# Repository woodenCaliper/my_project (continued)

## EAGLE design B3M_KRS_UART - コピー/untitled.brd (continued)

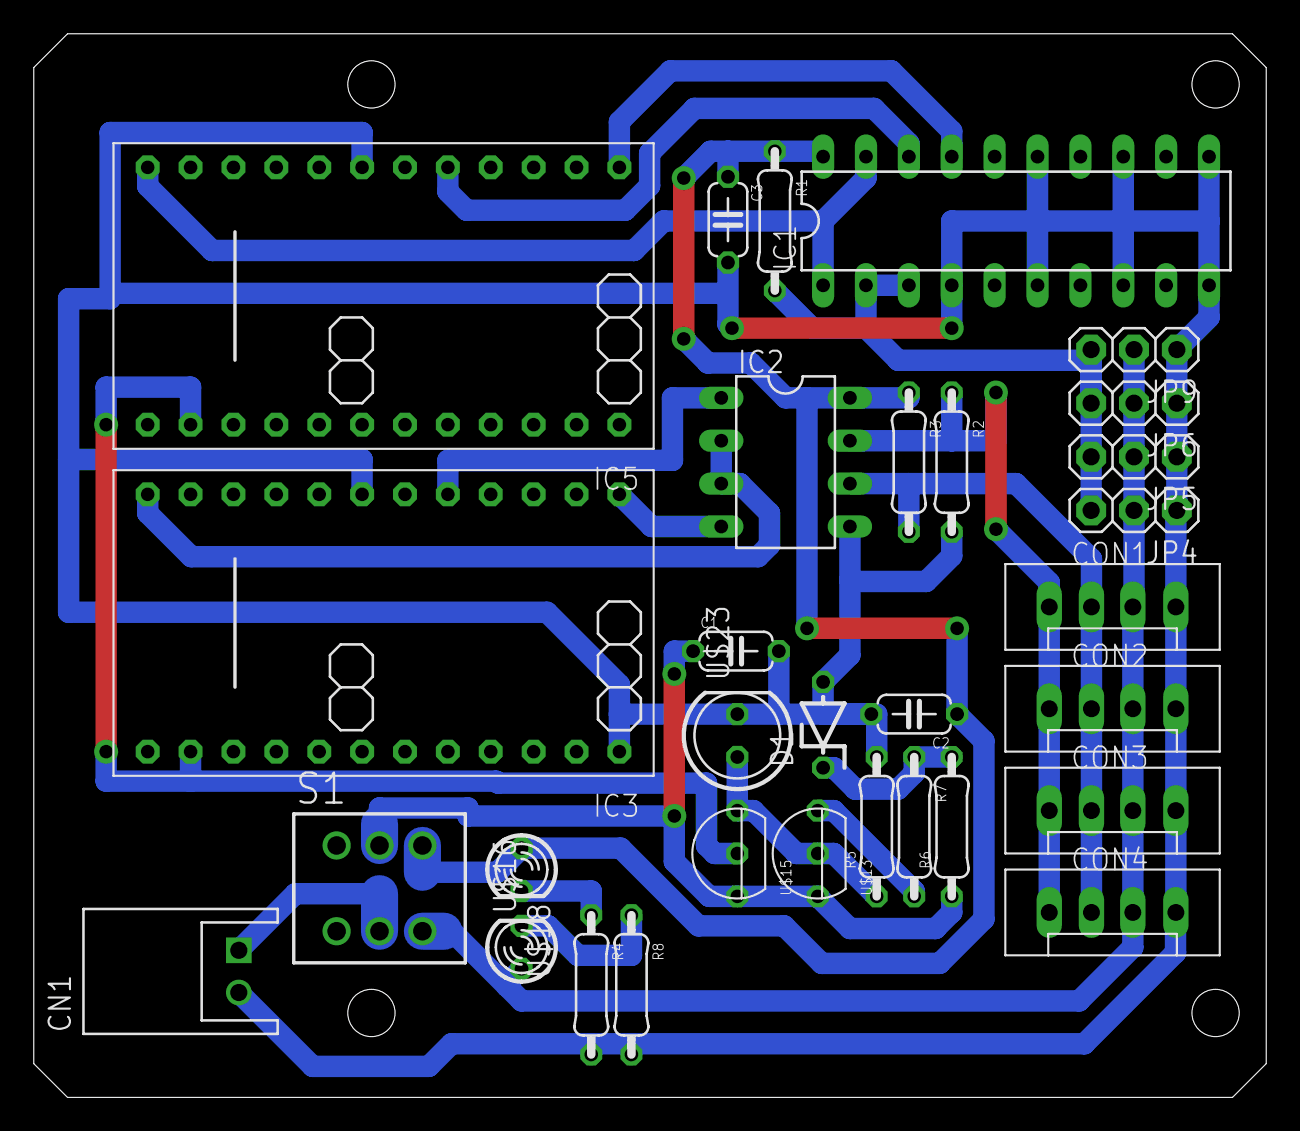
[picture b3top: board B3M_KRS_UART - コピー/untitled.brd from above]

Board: 2 copper layers, 73.0 x 63.0 mm, 31 parts (0 on the bottom side), 20 nets.

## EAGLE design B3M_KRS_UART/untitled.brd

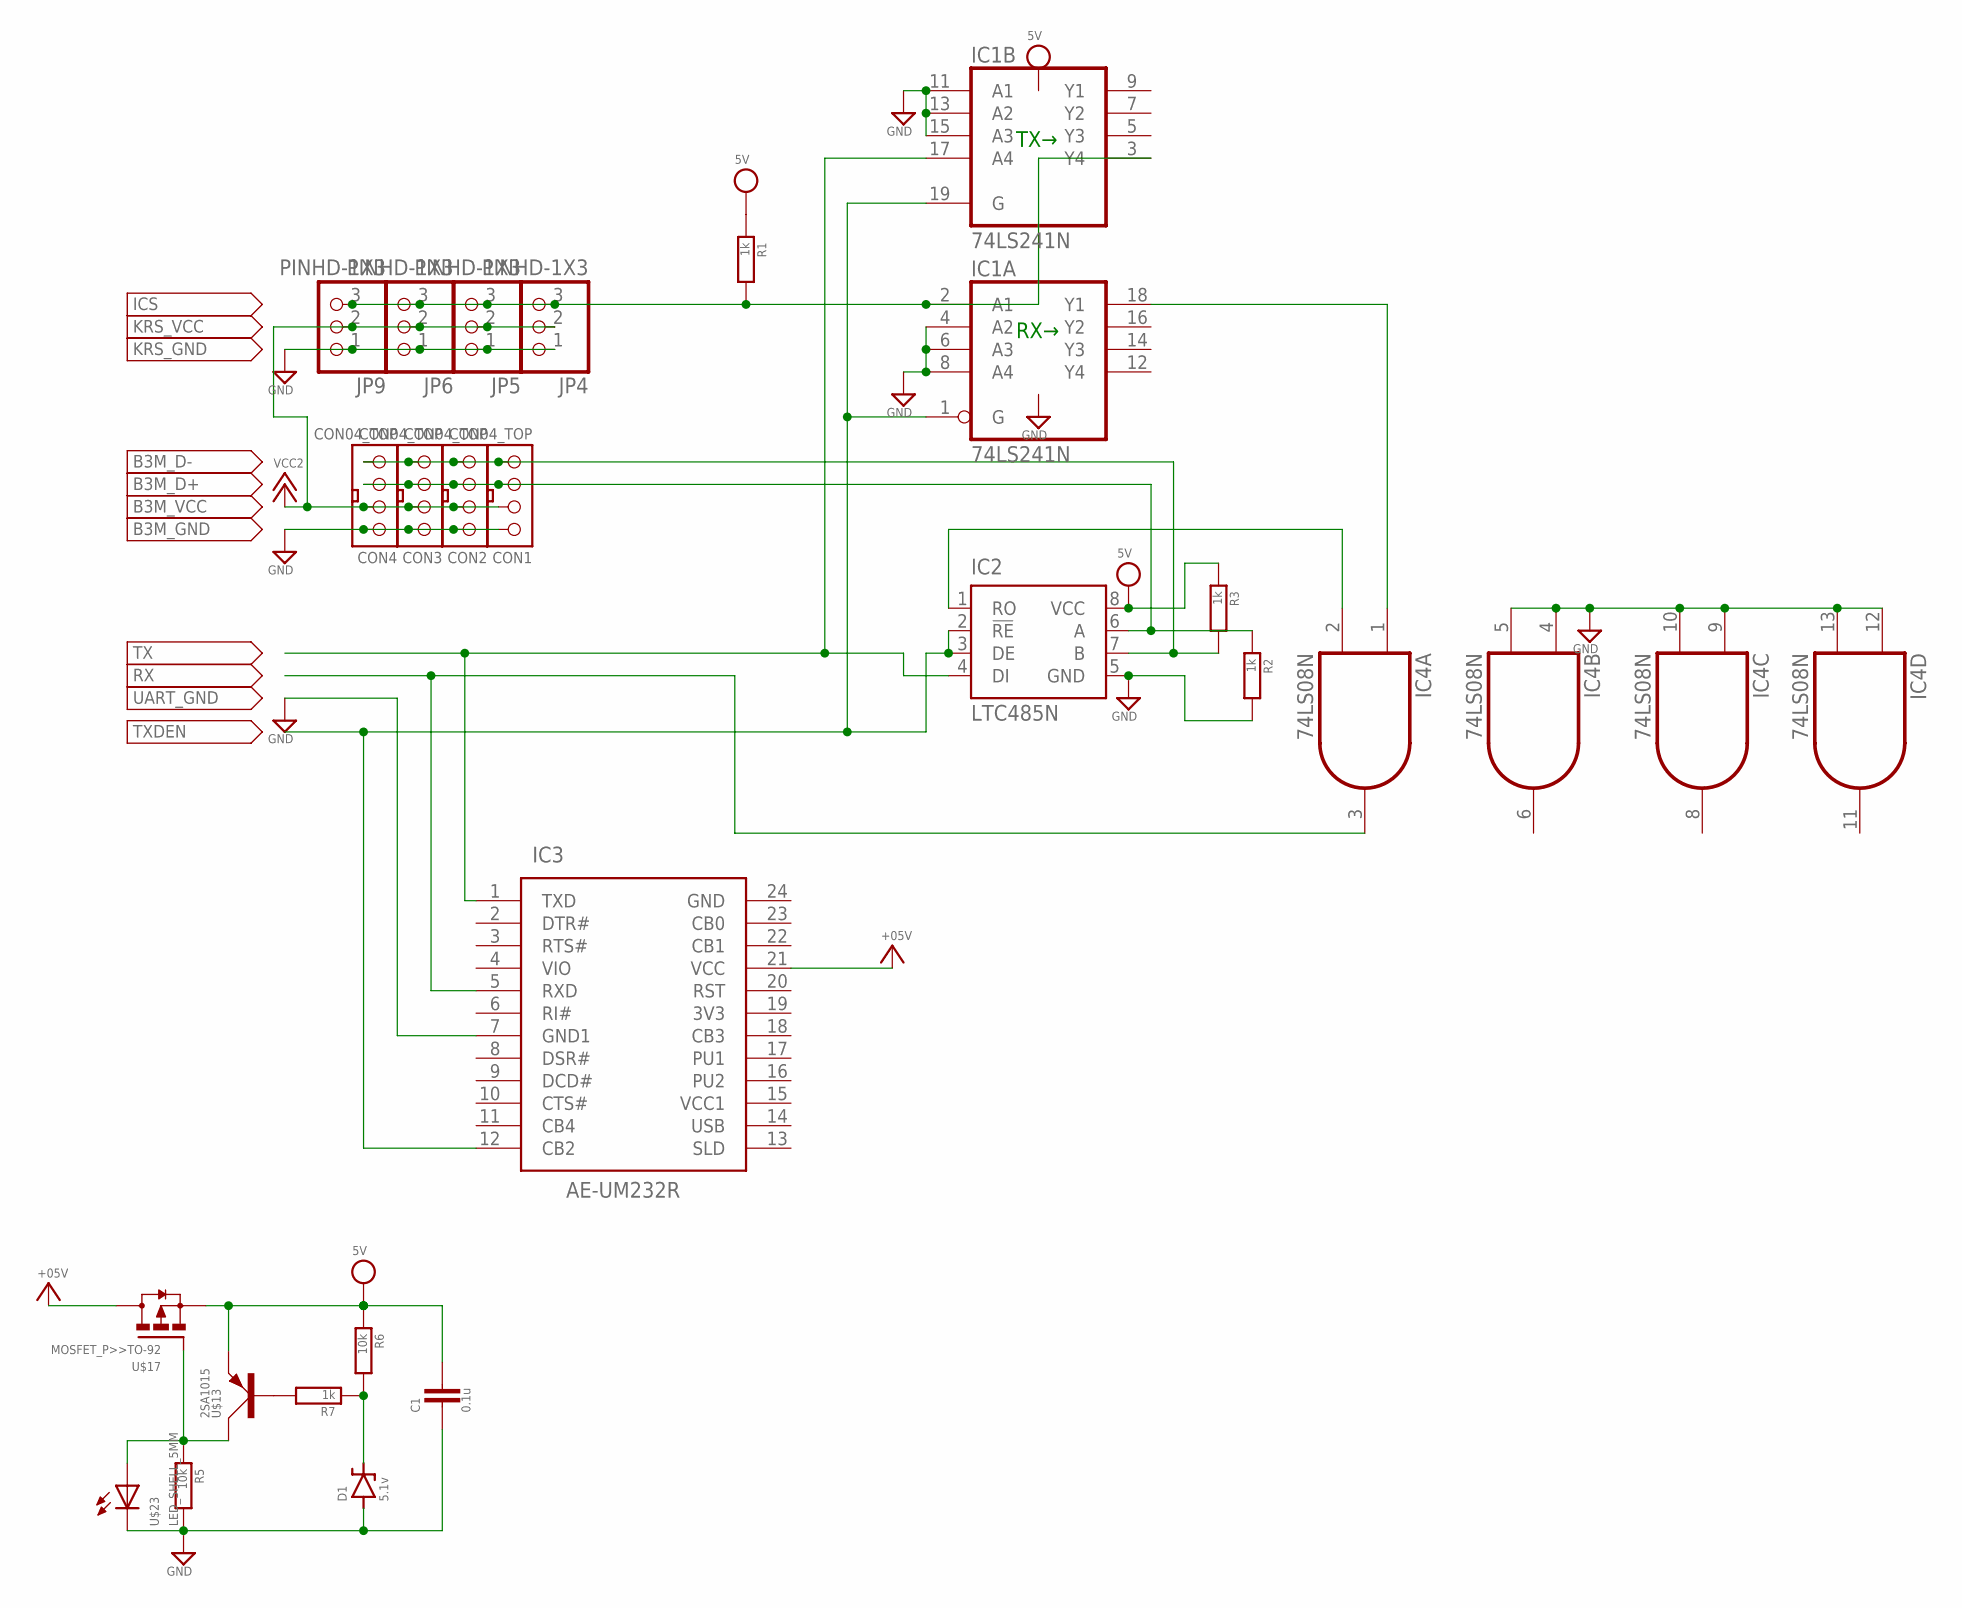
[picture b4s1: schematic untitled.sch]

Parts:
C1: 0.1u; C050-024X044
CON1, CON2, CON3, CON4: CON04_TOP; TOP_CON4
D1: 5.1v; ZDIO-5
IC1: 74LS241N; DIL20
IC2: LTC485N; DIL08
IC3: AE-UM232R
IC4: 74LS08N; DIL14
JP4, JP5, JP6, JP9: PINHD-1X3; 1X03
R1, R2, R3, R7: 1k; 1/4W(8MM)
R5, R6: 10k; 1/4W(8MM)
U$13: 2SA1015; TO-92
U$17: MOSFET_P>>TO-92; TO-92
U$23: LED_SHELL_5MM; 5MM

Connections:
+5V: IC3.21 (VCC), U$17.2 (D)
GND: C1.2, CON1.P$1 (1), CON2.P$1 (1), CON3.P$1 (1), CON4.P$1 (1), D1.A, IC1.4 (A2), IC1.6 (A3), IC1.8 (A4), IC1.10 (GND), IC1.11 (A1), IC1.13 (A2), IC1.15 (A3), IC2.5 (GND), IC3.7 (GND1), IC3.24 (GND), IC4.4 (I0), IC4.5 (I1), IC4.7 (GND), IC4.9 (I0), IC4.10 (I1), IC4.12 (I0), IC4.13 (I1), JP4.1, JP5.1, JP6.1, JP9.1, R2.2, R5.2, U$23.P$2 (C)
ICS: IC1.2 (A1), IC1.3 (Y4), JP4.3, JP5.3, JP6.3, JP9.3, R1.2
unnamed: IC1.18 (Y1), IC4.1 (I0)
unnamed: CON1.P$3 (3), CON2.P$3 (3), CON3.P$3 (3), CON4.P$3 (3), IC2.6 (A), R2.1
unnamed: IC2.1 (RO), IC4.2 (I1)
unnamed: R5.1, U$13.2 (C), U$17.1 (G), U$23.P$1 (A)
unnamed: D1.C, R6.2, R7.1
unnamed: R7.2, U$13.3 (B)
unnamed: CON1.P$4 (4), CON2.P$4 (4), CON3.P$4 (4), CON4.P$4 (4), IC2.7 (B), R3.2
RXD: IC3.5 (RXD), IC4.3 (O)
TXD: IC1.17 (A4), IC2.4 (DI), IC3.1 (TXD)
TXDEN: IC1.1 (G), IC1.19 (G), IC2.2 (!RE), IC2.3 (DE), IC3.12 (CB2)
VCC: C1.1, IC1.20 (VCC), IC2.8 (VCC), IC4.14 (VCC), R1.1, R3.1, R6.1, U$13.1 (E), U$17.3 (S)
VCC1: IC3.15 (VCC1)
VCC2: CON1.P$2 (2), CON2.P$2 (2), CON3.P$2 (2), CON4.P$2 (2), JP4.2, JP5.2, JP6.2, JP9.2

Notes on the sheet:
RX→
TX→

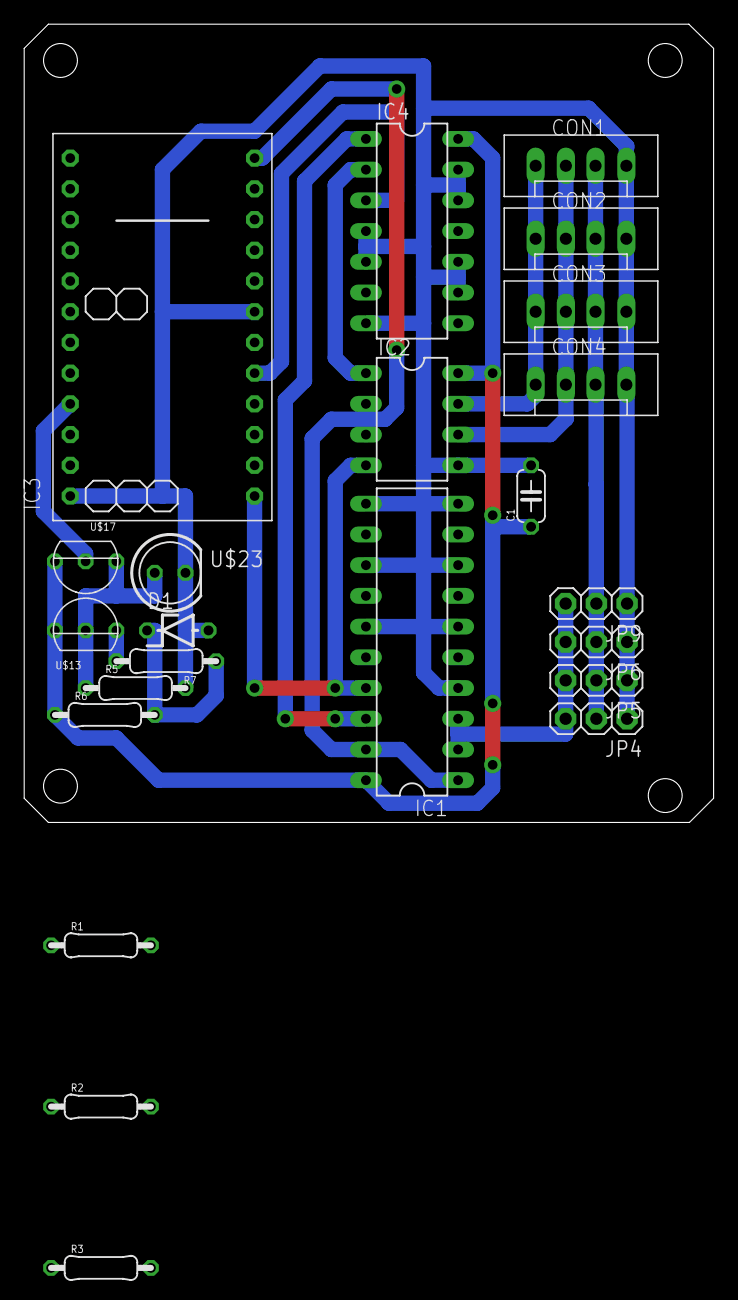
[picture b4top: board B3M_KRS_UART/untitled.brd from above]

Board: 2 copper layers, 57.0 x 66.0 mm, 23 parts (0 on the bottom side), 15 nets.

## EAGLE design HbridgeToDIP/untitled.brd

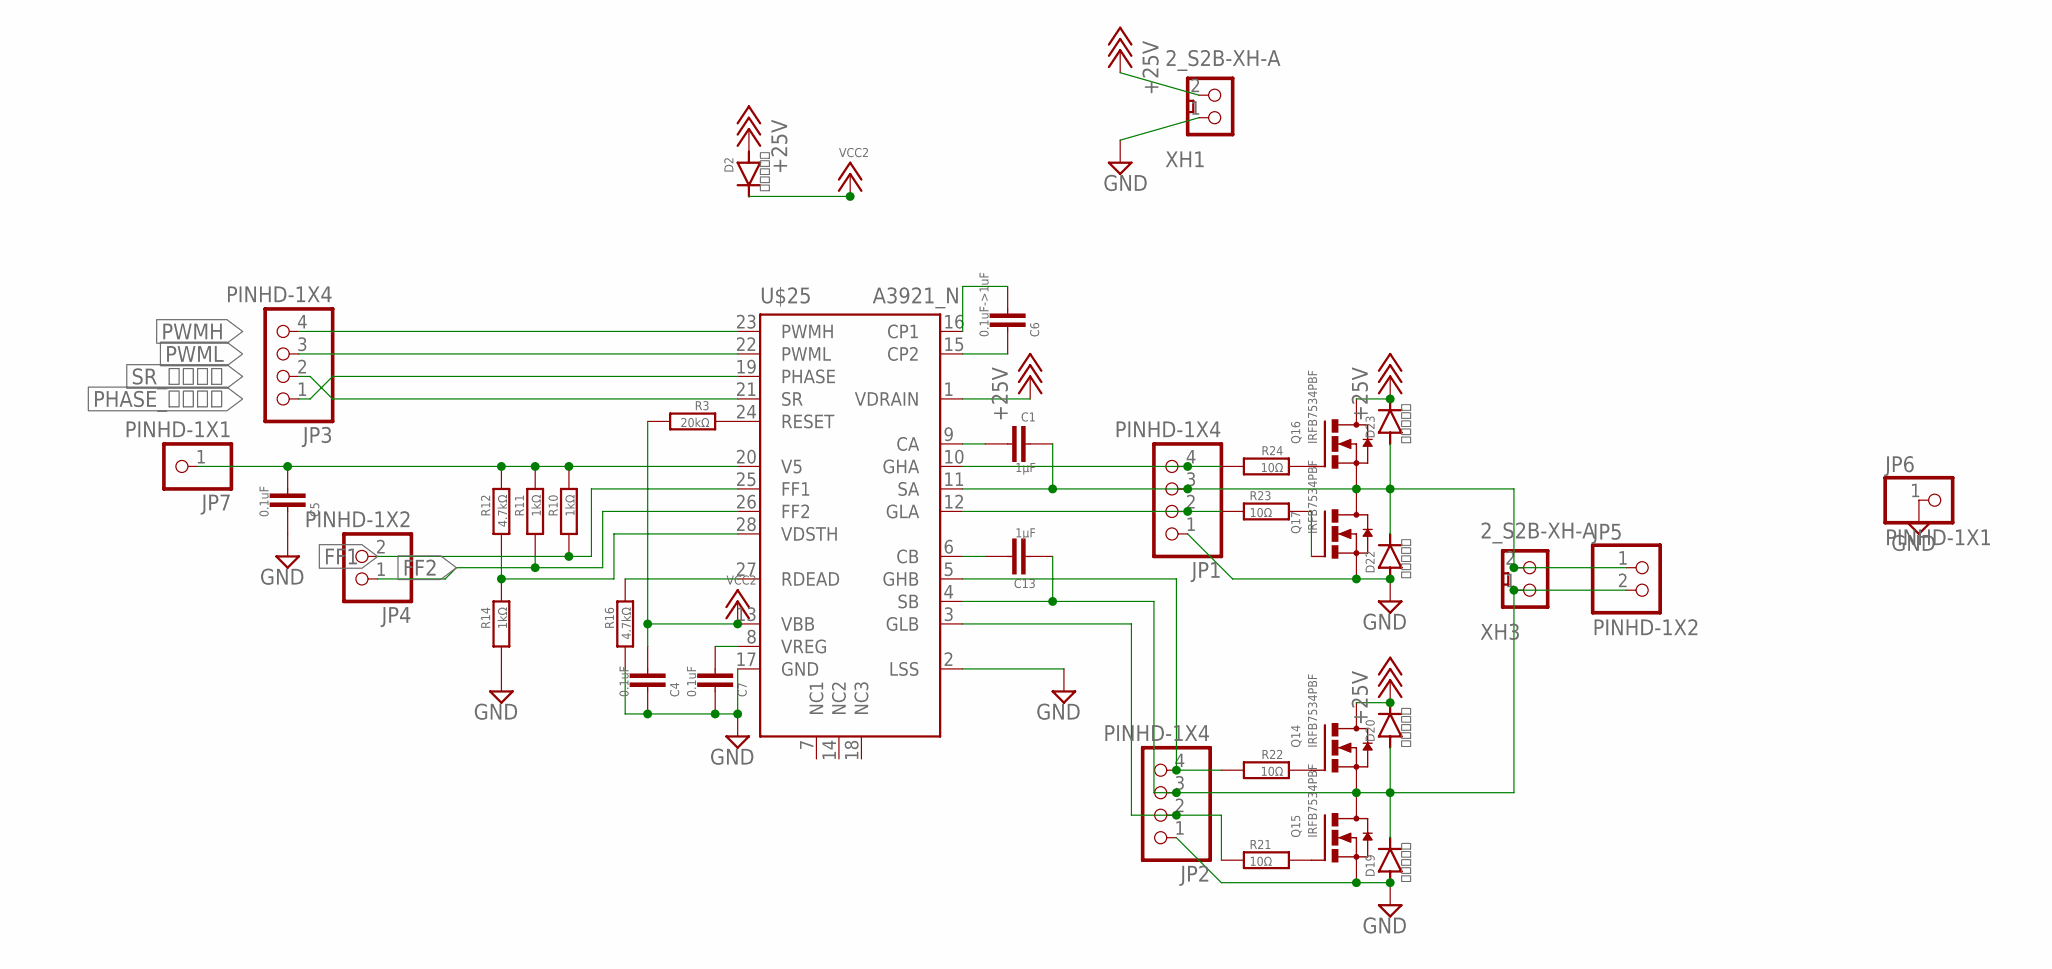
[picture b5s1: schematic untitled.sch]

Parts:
C1, C13: 1μF; 2012
C4, C5, C7: 0.1uF; 2012
C6: 0.1uF->1uF; 2012
D2, D19, D20, D22, D23: ＭＳ１８Ｆ; MS18F
JP1, JP2, JP3: PINHD-1X4; 1X04
JP4, JP5: PINHD-1X2; 1X02
JP6, JP7: PINHD-1X1; 1X01
Q14, Q15, Q16, Q17: IRFB7534PBF; TO252
R3: 20kΩ; 2012
R10, R11, R14: 1kΩ; 2012
R12, R16: 4.7kΩ; 2012
R21, R22, R23, R24: 10Ω; 2012
U$25: A3921_N; TSSOP28_N
XH1, XH3: 2_S2B-XH-A; S2B-XH-A

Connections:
+18V: D2.P$1 (A), D20.P$2 (C), D23.P$2 (C), Q14.3 (D), Q16.3 (D), U$25.1 (VDRAIN), XH1.2
FF1: JP4.2, R10.2, U$25.25 (FF1)
FF2: JP4.1, R11.2, U$25.26 (FF2)
GND: C4.2, C5.2, C7.2, D19.P$1 (A), D22.P$1 (A), JP1.1, JP2.1, JP6.1, Q15.2 (S), Q17.2 (S), R14.2, R16.2, U$25.2 (LSS), U$25.17 (GND), XH1.1
unnamed: C6.1, U$25.16 (CP1)
unnamed: JP2.4, R22.2, U$25.5 (GHB)
unnamed: C1.2, D22.P$2 (C), D23.P$1 (A), JP1.3, JP5.1, Q16.2 (S), Q17.3 (D), U$25.11 (SA), XH3.2
unnamed: JP2.2, R21.1, U$25.3 (GLB)
unnamed: C1.1, U$25.9 (CA)
unnamed: JP1.4, R24.2, U$25.10 (GHA)
unnamed: C13.2, D19.P$2 (C), D20.P$1 (A), JP2.3, JP5.2, Q14.2 (S), Q15.3 (D), U$25.4 (SB), XH3.1
unnamed: C6.2, U$25.15 (CP2)
unnamed: JP1.2, R23.1, U$25.12 (GLA)
unnamed: R3.1, U$25.24 (RESET)
unnamed: C7.1, U$25.8 (VREG)
unnamed: C13.1, U$25.6 (CB)
unnamed: R12.2, R14.1, U$25.28 (VDSTH)
unnamed: Q15.1 (G), R21.2
unnamed: R16.1, U$25.27 (RDEAD)
unnamed: Q14.1 (G), R22.1
unnamed: Q17.1 (G), R23.2
unnamed: Q16.1 (G), R24.1
PHASE_正転逆転: JP3.1, U$25.19 (PHASE)
PWMH: JP3.4, U$25.23 (PWMH)
PWML: JP3.3, U$25.22 (PWML)
SR_ブレーキ: JP3.2, U$25.21 (SR)
V5: C5.1, JP7.1, R10.1, R11.1, R12.1, U$25.20 (V5)
VCC2: C4.1, D2.P$2 (C), R3.2, U$25.13 (VBB)

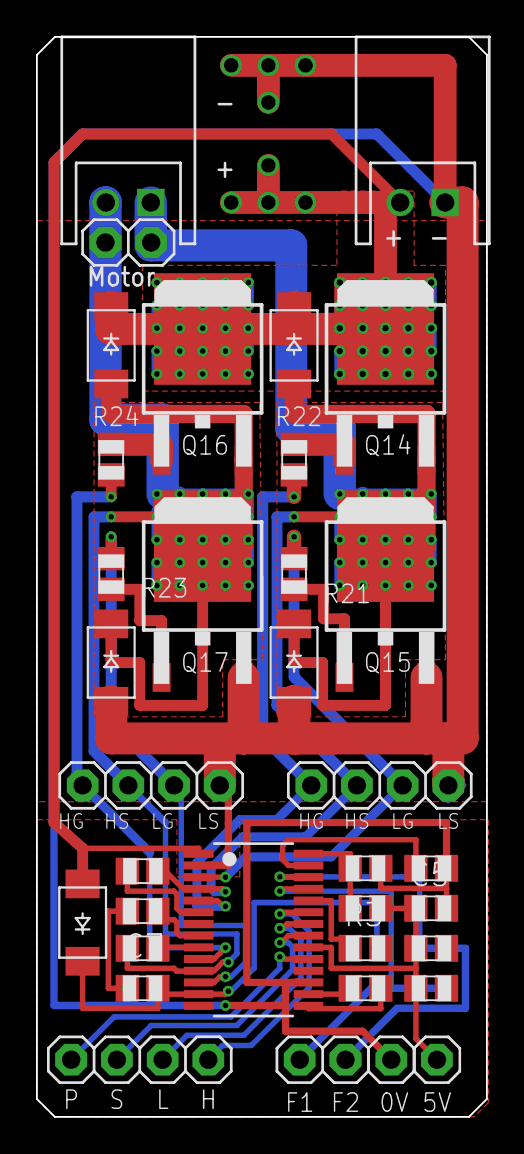
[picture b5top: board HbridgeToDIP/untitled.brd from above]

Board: 2 copper layers, 25.0 x 60.0 mm, 35 parts (0 on the bottom side), 28 nets.

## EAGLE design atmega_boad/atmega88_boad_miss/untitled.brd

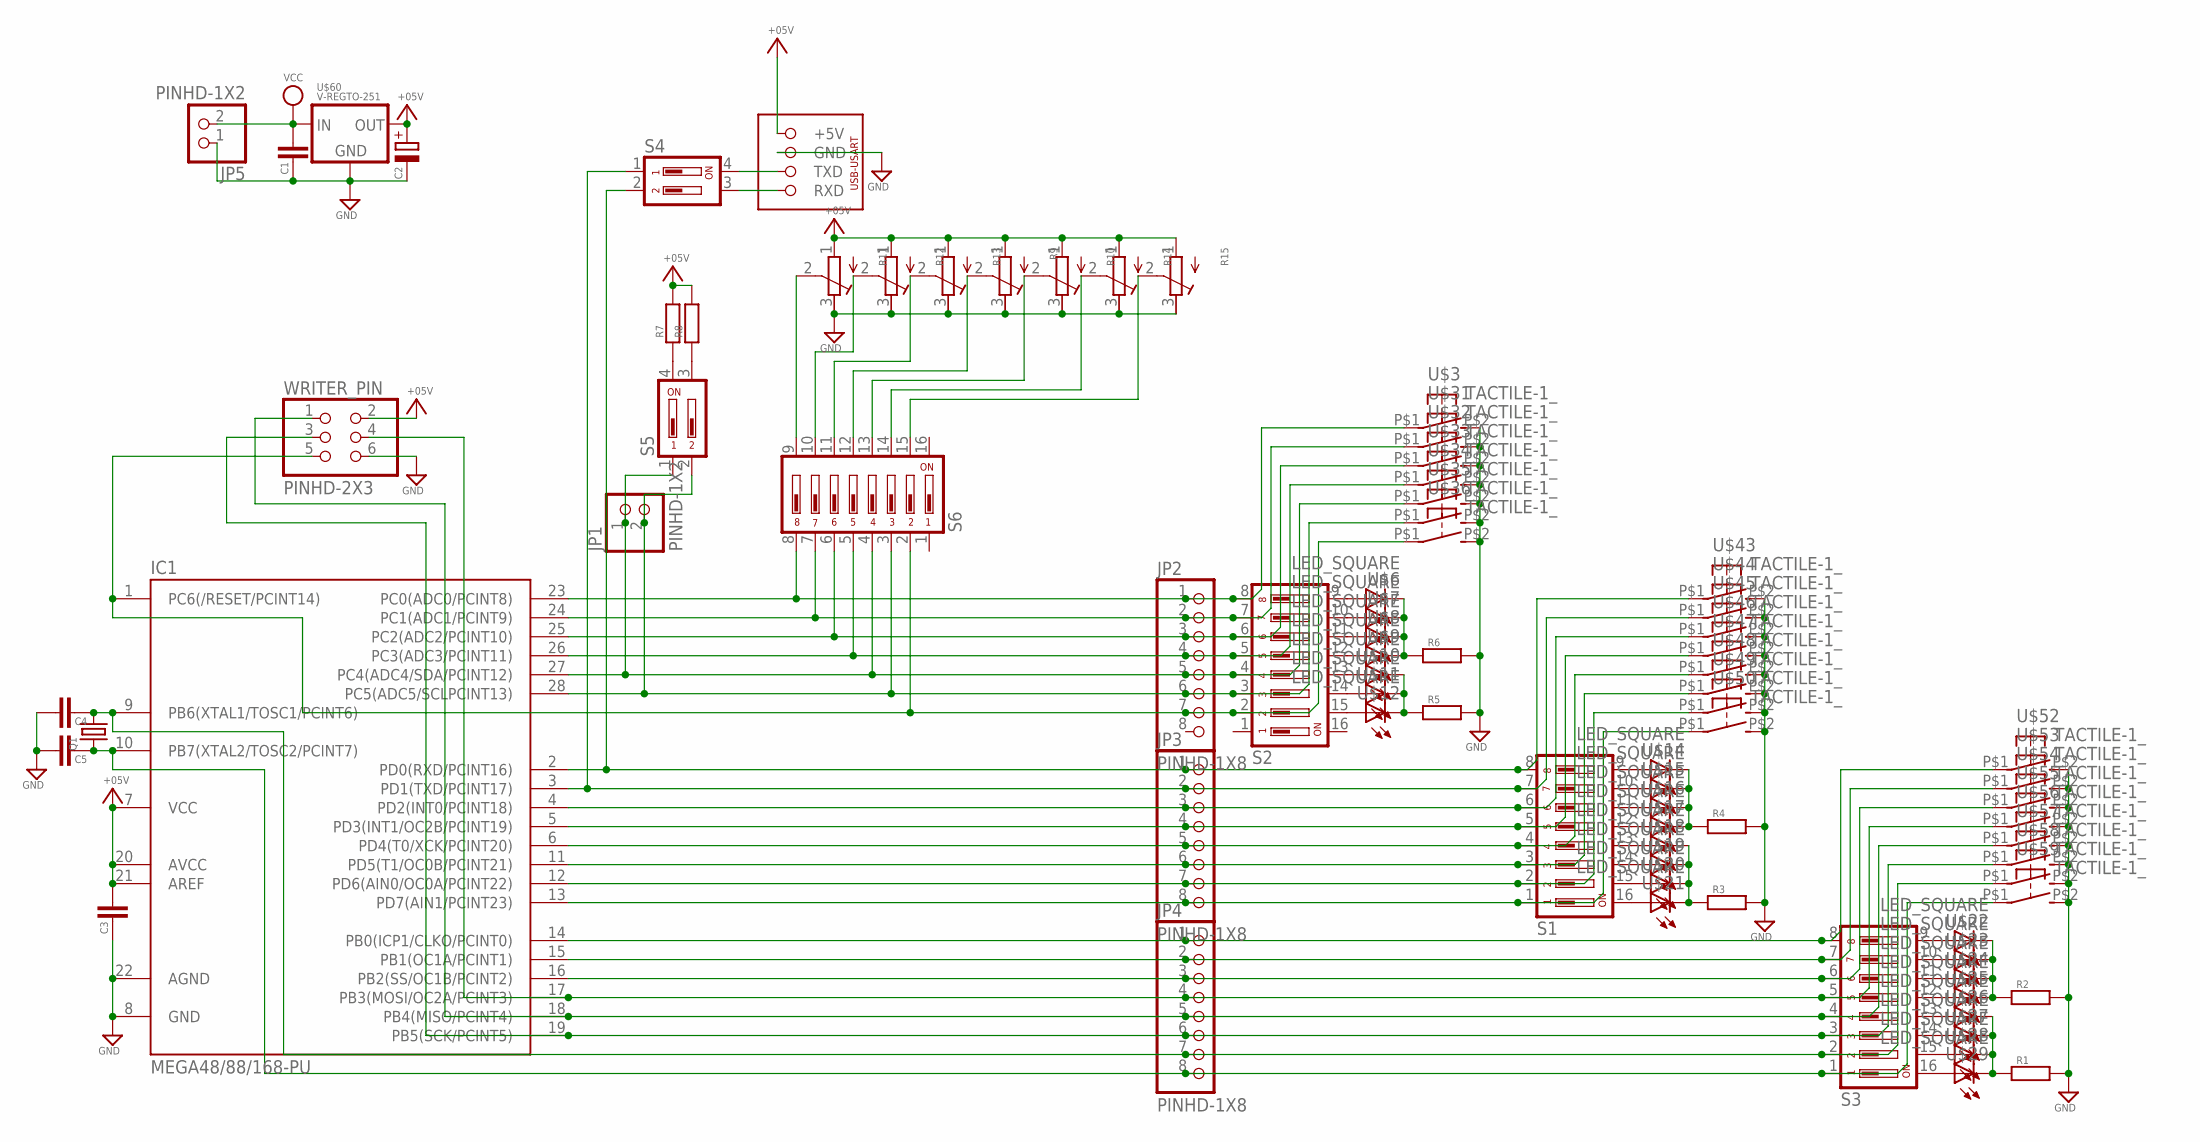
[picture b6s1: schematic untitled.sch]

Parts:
C1, C3, C4, C5: C-025-025X050; C025-025X050
C2: CPOL-E2.5-6; E2,5-6
IC1: MEGA48/88/168-PU; DIL28-3
JP1, JP5: PINHD-1X2; 1X02
JP2, JP3, JP4: PINHD-1X8; 1X08
Q1: CRYSTALHC49S; HC49/S
R1, R2, R3, R4, R5, R6, R7, R8: R-EU_1/4W(8MM); 1/4W(8MM)
R9, R10, R11, R12, R13, R14, R15: R-TRIMM_3339P; 3339P
S1, S2, S3, S6: DIP08YL
S4, S5: DIP02YL
U$3, U$31, U$32, U$33, U$34, U$35, U$36, U$43, U$44, U$45, U$46, U$47, U$48, U$49, U$50, U$52, U$53, U$54, U$55, U$56, U$57, U$58, U$59: TACTILE-1_; TACTILE_
U$6, U$7, U$8, U$9, U$10, U$11, U$12, U$14, U$15, U$16, U$17, U$18, U$19, U$20, U$21, U$22, U$23, U$24, U$25, U$26, U$27, U$28, U$29: LED_SQUARE; 5020
U$60: V-REGTO-251; TO-251
U$64: AE-FT234X
WRITER_PIN: PINHD-2X3; 2X03

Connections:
+5V: C2.+, C3.1, IC1.7 (VCC), IC1.20 (AVCC), IC1.21 (AREF), R7.2, R8.2, R9.1 (E), R10.1 (E), R11.1 (E), R12.1 (E), R13.1 (E), R14.1 (E), R15.1 (E), U$60.3 (OUT), U$64.P$1 (+5V), WRITER_PIN.2
GND: C1.2, C2.-, C3.2, C4.1, C5.1, IC1.8 (GND), IC1.22 (AGND), JP5.1, R1.2, R2.2, R3.2, R4.2, R5.2, R6.2, R9.3 (A), R10.3 (A), R11.3 (A), R12.3 (A), R13.3 (A), R14.3 (A), R15.3 (A), U$3.P$2 (S), U$31.P$2 (S), U$32.P$2 (S), U$33.P$2 (S), U$34.P$2 (S), U$35.P$2 (S), U$36.P$2 (S), U$43.P$2 (S), U$44.P$2 (S), U$45.P$2 (S), U$46.P$2 (S), U$47.P$2 (S), U$48.P$2 (S), U$49.P$2 (S), U$50.P$2 (S), U$52.P$2 (S), U$53.P$2 (S), U$54.P$2 (S), U$55.P$2 (S), U$56.P$2 (S), U$57.P$2 (S), U$58.P$2 (S), U$59.P$2 (S), U$60.2 (GND), U$64.P$2 (GND), WRITER_PIN.6
unnamed: IC1.2 (PD0(RXD/PCINT16)), JP3.1, S1.8, S4.2, U$43.P$1
unnamed: IC1.3 (PD1(TXD/PCINT17)), JP3.2, S1.7, S4.1, U$44.P$1
unnamed: IC1.4 (PD2(INT0/PCINT18)), JP3.3, S1.6, U$45.P$1
unnamed: IC1.5 (PD3(INT1/OC2B/PCINT19)), JP3.4, S1.5, U$46.P$1
unnamed: IC1.6 (PD4(T0/XCK/PCINT20)), JP3.5, S1.4, U$47.P$1
unnamed: IC1.11 (PD5(T1/OC0B/PCINT21)), JP3.6, S1.3, U$48.P$1
unnamed: IC1.12 (PD6(AIN0/OC0A/PCINT22)), JP3.7, S1.2, U$49.P$1
unnamed: IC1.13 (PD7(AIN1/PCINT23)), JP3.8, S1.1, U$50.P$1
unnamed: IC1.28 (PC5(ADC5/SCLPCINT13)), JP1.2, JP2.6, S2.3, S5.2, S6.3, U$35.P$1
unnamed: IC1.27 (PC4(ADC4/SDA/PCINT12)), JP1.1, JP2.5, S2.4, S5.1, S6.4, U$34.P$1
unnamed: IC1.26 (PC3(ADC3/PCINT11)), JP2.4, S2.5, S6.5, U$33.P$1
unnamed: IC1.25 (PC2(ADC2/PCINT10)), JP2.3, S2.6, S6.6, U$32.P$1
unnamed: IC1.24 (PC1(ADC1/PCINT9)), JP2.2, S2.7, S6.7, U$31.P$1
unnamed: IC1.23 (PC0(ADC0/PCINT8)), JP2.1, S2.8, S6.8, U$3.P$1
unnamed: IC1.19 (PB5(SCK/PCINT5)), JP4.6, S3.3, U$57.P$1, WRITER_PIN.3
unnamed: IC1.18 (PB4(MISO/PCINT4)), JP4.5, S3.4, U$56.P$1, WRITER_PIN.1
unnamed: IC1.17 (PB3(MOSI/OC2A/PCINT3)), JP4.4, S3.5, U$55.P$1, WRITER_PIN.4
unnamed: IC1.16 (PB2(SS/OC1B/PCINT2)), JP4.3, S3.6, U$54.P$1
unnamed: IC1.15 (PB1(OC1A/PCINT1)), JP4.2, S3.7, U$53.P$1
unnamed: IC1.14 (PB0(ICP1/CLKO/PCINT0)), JP4.1, S3.8, U$52.P$1
unnamed: IC1.1 (PC6(/RESET/PCINT14)), JP2.7, S2.2, S6.2, U$36.P$1, WRITER_PIN.5
unnamed: C4.2, IC1.9 (PB6(XTAL1/TOSC1/PCINT6)), JP4.7, Q1.2, S3.2, U$58.P$1
unnamed: S2.9, U$6.P$1 (A)
unnamed: S2.10, U$7.P$1 (A)
unnamed: S2.11, U$8.P$1 (A)
unnamed: S2.12, U$9.P$1 (A)
unnamed: S2.13, U$10.P$1 (A)
unnamed: S2.14, U$11.P$1 (A)
unnamed: S2.15, U$12.P$1 (A)
unnamed: S4.4, U$64.P$3 (TXD)
unnamed: S1.9, U$14.P$1 (A)
unnamed: S1.10, U$15.P$1 (A)
unnamed: S1.11, U$16.P$1 (A)
unnamed: S1.12, U$17.P$1 (A)
unnamed: S1.13, U$18.P$1 (A)
unnamed: S1.14, U$19.P$1 (A)
unnamed: S1.15, U$20.P$1 (A)
unnamed: S1.16, U$21.P$1 (A)
unnamed: S3.9, U$22.P$1 (A)
unnamed: S3.10, U$23.P$1 (A)
unnamed: S3.11, U$24.P$1 (A)
unnamed: S3.12, U$25.P$1 (A)
unnamed: S3.13, U$26.P$1 (A)
unnamed: S3.14, U$27.P$1 (A)
unnamed: S3.15, U$28.P$1 (A)
unnamed: S3.16, U$29.P$1 (A)
unnamed: R1.1, U$26.P$2 (C), U$27.P$2 (C), U$28.P$2 (C), U$29.P$2 (C)
unnamed: R2.1, U$22.P$2 (C), U$23.P$2 (C), U$24.P$2 (C), U$25.P$2 (C)
unnamed: R3.1, U$18.P$2 (C), U$19.P$2 (C), U$20.P$2 (C), U$21.P$2 (C)
unnamed: R4.1, U$14.P$2 (C), U$15.P$2 (C), U$16.P$2 (C), U$17.P$2 (C)
unnamed: R5.1, U$10.P$2 (C), U$11.P$2 (C), U$12.P$2 (C)
unnamed: R6.1, U$6.P$2 (C), U$7.P$2 (C), U$8.P$2 (C), U$9.P$2 (C)
unnamed: S4.3, U$64.P$4 (RXD)
unnamed: R7.1, S5.4
unnamed: R8.1, S5.3
unnamed: R11.2 (S), S6.9
unnamed: R12.2 (S), S6.10
unnamed: R13.2 (S), S6.11
unnamed: R9.2 (S), S6.12
unnamed: R10.2 (S), S6.13
unnamed: R14.2 (S), S6.14
unnamed: R15.2 (S), S6.15
unnamed: C5.2, IC1.10 (PB7(XTAL2/TOSC2/PCINT7)), JP4.8, Q1.1, S3.1, U$59.P$1
VCC: C1.1, JP5.2, U$60.1 (IN)

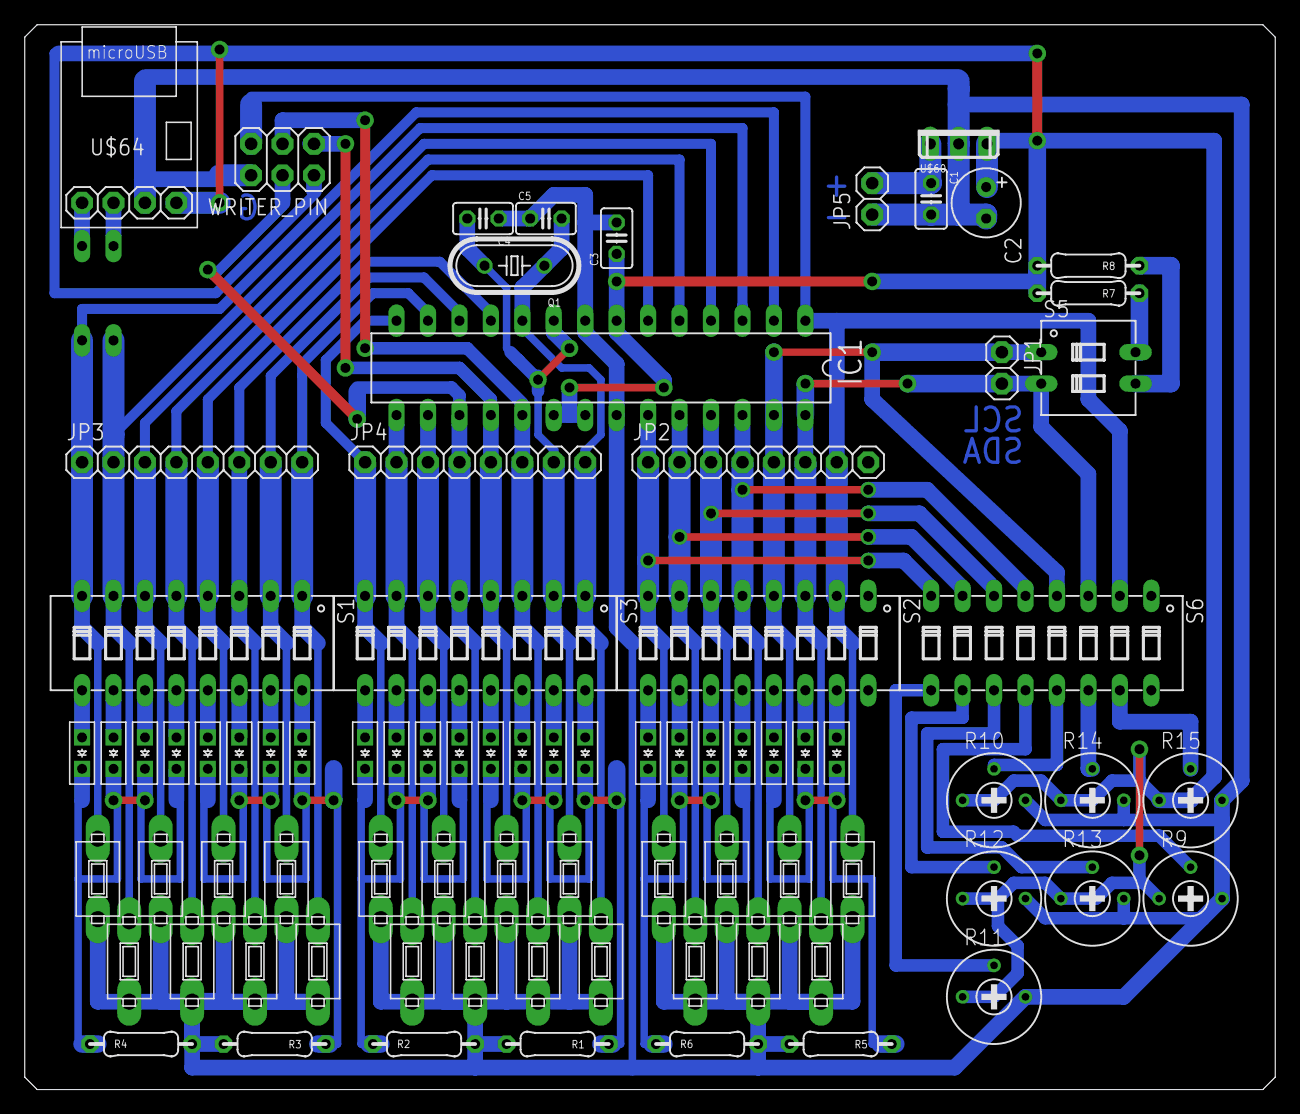
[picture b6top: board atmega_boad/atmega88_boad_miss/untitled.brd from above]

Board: 2 copper layers, 101.0 x 86.0 mm, 82 parts (1 on the bottom side), 66 nets.
